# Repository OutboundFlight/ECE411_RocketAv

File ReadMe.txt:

Overview:

This GitHub provides documentation for the design, implemation, and use of the TinyAV
Amateur Avionics System. The TinyAV is a printed circuit board that includes a 
microcontroller, acellerometer, gyroscope, magnetometer, temperature sensor, flash
memory storage, and a rechargeable lithium-ion battery. It allows for a portable way 
to record flight data that can be use for flight analysis on model rockets.

----------------------------------------------------------------------------------------------

Table Of Contents:

Assignments - Team exercises assigned in ECE 411
Doc         - Project Proposals, Project Requirements, UML Diagrams, Testing Documentation, 
	      Project Schedules, & Bill Of Materials
Eagle       - Schematic & Board Layout Documentation
Launch_Data - Test Launch Raw Data & Analysis Graphs
Ref	    - Reference Documentation For Board Creation
Src	    - Libraries & Source Code For The TinyAv Board

----------------------------------------------------------------------------------------------

Useful Links:

Lab for Interconnected Devices: http://psu-epl.github.io/
Arduino Software: https://www.arduino.cc/

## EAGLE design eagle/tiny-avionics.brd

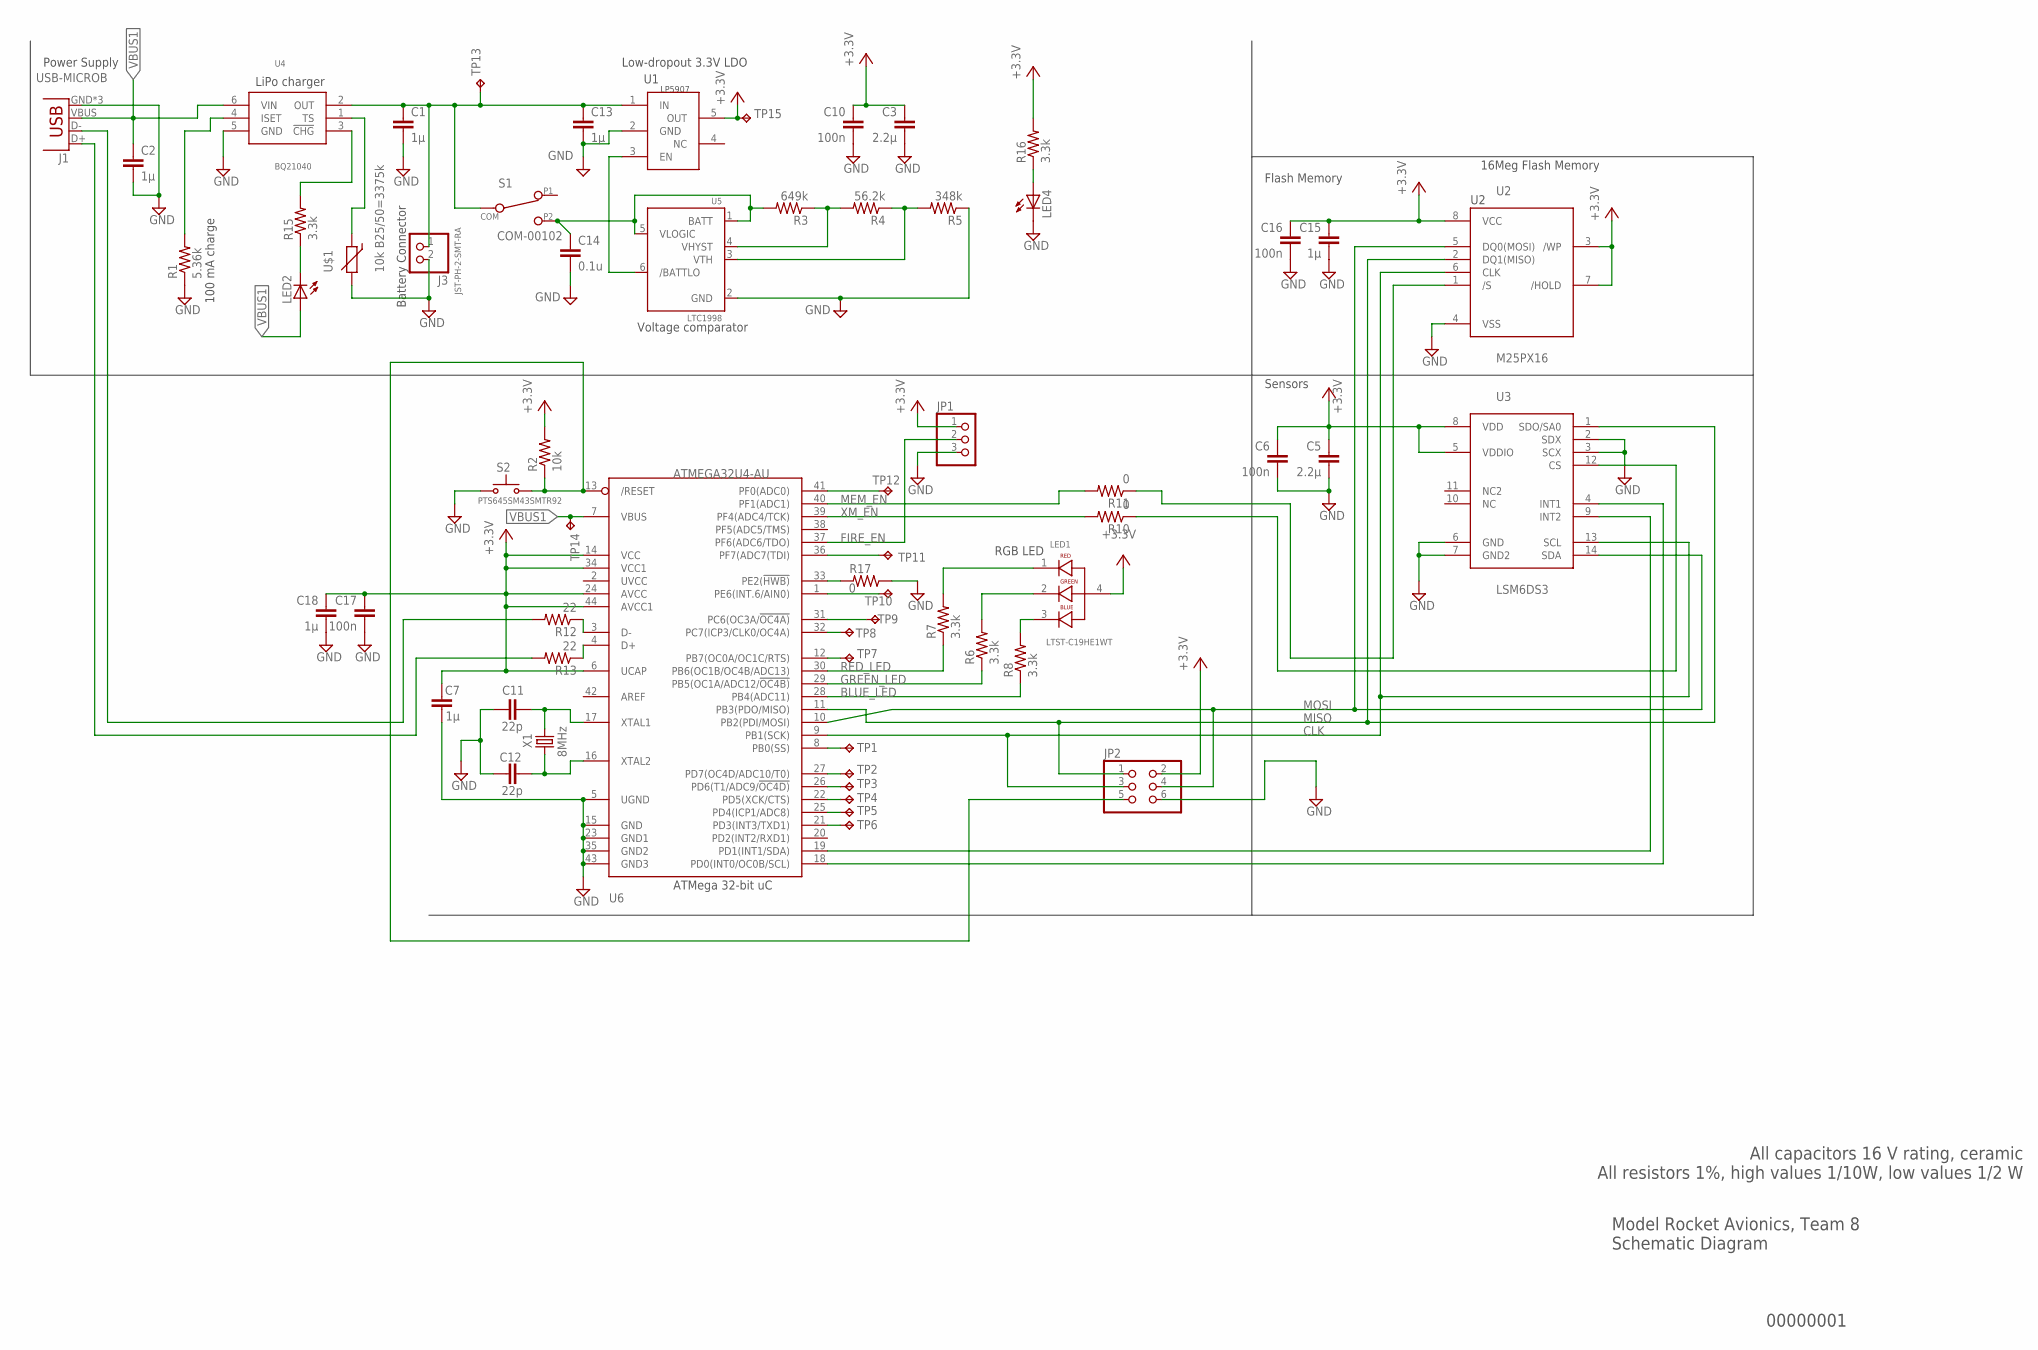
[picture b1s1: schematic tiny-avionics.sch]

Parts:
C1, C2, C7, C13, C15, C18: 1µ; C0603
C3, C5: 2.2µ; C0603
C6, C10, C16, C17: 100n; C0603
C11, C12: 22p; C0603
C14: 0.1u; C0603
J1: USB-MICROB
J3: JST-PH-2-SMT-RA
JP1: PINHD-1X3; 1X03
JP2: PINHD-2X3; 2X03
LED1: LTST-C19HE1WT; LEDSC85P160X160X35-4N
LED2, LED4: LEDCHIP-LED0603; CHIP-LED0603
R1: 5.36k; R0603
R2: 10k; R0603
R3: 649k; R0603
R4: 56.2k; R0603
R5: 348k; R0603
R6, R7, R8, R15, R16: 3.3k; R0603
R10, R11, R17: 0; R0603
R12, R13: 22; R0603
S1: COM-00102; ESWITCH
S2: PTS645SM43SMTR92; PTS645-SMD; MPN PTS645SM43SMTR92 LFS
TP1, TP2, TP3, TP4, TP5, TP6, TP7, TP8, TP9, TP10, TP11, TP12, TP13, TP14, TP15: TPTP08R; TP08R
U1: LP5907; SOT23-5L
U2: M25PX16; SO8
U3: LSM6DS3; LGA-14L
U4: BQ21040; SOT23-6L
U5: LTC1998; TSOT23-6
U6: ATMEGA32U4-AU; TQFP44
U$1: 10k B25/50=3375k; R0603
X1: 8MHz; ATS-SM; MPN ATS080B

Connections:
BLUE_LED: R8.1, U6.28 (PB4(ADC11))
CLK: JP2.3, U2.6 (CLK), U3.13 (SCL), U6.9 (PB1(SCK))
D+: J1.D+, R13.2
D-: J1.D-, R12.2
FIRE_EN: JP1.2, U6.37 (PF6(ADC6/TDO))
GND: C1.2, C2.2, C3.2, C5.2, C6.2, C7.2, C10.2, C11.2, C12.2, C13.2, C14.2, C15.2, C16.2, C17.2, C18.2, J1.GND, J1.MT1 (GND), J1.MT2 (GND), J3.2 (1), JP1.3, JP2.6, LED4.C, R1.1, R5.1, R17.1, S2.1, S2.2, U1.2 (GND), U2.4 (VSS), U3.2 (SDX), U3.3 (SCX), U3.6 (GND), U3.7 (GND2), U4.5 (GND), U5.2 (GND), U6.5 (UGND), U6.15 (GND), U6.23 (GND1), U6.35 (GND2), U6.43 (GND3), U$1.2
GREEN_LED: R6.1, U6.29 (PB5(OC1A/ADC12/!OC4B))
MEM_EN: R11.1, U2.1 (/S)
MISO: JP2.1, U2.2 (DQ1(MISO)), U3.1 (SDO/SA0), U6.11 (PB3(PDO/MISO))
MOSI: JP2.4, U2.5 (DQ0(MOSI)), U3.14 (SDA), U6.10 (PB2(PDI/MOSI))
unnamed: LED1.1, R7.2
unnamed: C11.1, U6.17 (XTAL1), X1.1
unnamed: JP2.5, R2.1, S2.3 (S), S2.4 (S), U6.13 (/RESET)
unnamed: R15.2, U4.3 (!CHG)
unnamed: C12.1, U6.16 (XTAL2), X1.2
unnamed: R12.1, U6.3 (D-)
unnamed: LED1.2, R6.2
unnamed: LED1.3, R8.2
unnamed: U4.1 (TS), U$1.1
unnamed: U3.4 (INT1), U6.18 (PD0(INT0/OC0B/SCL))
unnamed: U3.9 (INT2), U6.19 (PD1(INT1/SDA))
unnamed: R3.1, R4.2, U5.4 (VHYST)
unnamed: C1.1, C13.1, J3.1 (2), S1.2 (COM), TP13.TP, U1.1 (IN), U4.2 (OUT)
unnamed: R4.1, R5.2, U5.3 (VTH)
unnamed: C14.1, R3.2, S1.3 (P2), U5.1 (BATT), U5.5 (VLOGIC)
unnamed: U1.3 (EN), U5.6 (/BATTLO)
unnamed: R10.2, U6.39 (PF4(ADC4/TCK))
unnamed: R11.2, U6.40 (PF1(ADC1))
unnamed: R13.1, U6.4 (D+)
unnamed: LED2.C, R15.1
unnamed: R1.2, U4.4 (ISET)
unnamed: LED4.A, R16.1
unnamed: R17.2, U6.33 (PE2(!HWB))
RED_LED: R7.1, U6.30 (PB6(OC1B/OC4B/ADC13))
TP1: TP1.TP, U6.8 (PB0(SS))
TP2: TP2.TP, U6.27 (PD7(OC4D/ADC10/T0))
TP3: TP3.TP, U6.26 (PD6(T1/ADC9/!OC4D))
TP4: TP4.TP, U6.22 (PD5(XCK/CTS))
TP5: TP5.TP, U6.25 (PD4(ICP1/ADC8))
TP6: TP6.TP, U6.21 (PD3(INT3/TXD1))
TP7: TP7.TP, U6.12 (PB7(OC0A/OC1C/RTS))
TP8: TP8.TP, U6.32 (PC7(ICP3/CLK0/OC4A))
TP9: TP9.TP, U6.31 (PC6(OC3A/!OC4A))
TP10: TP10.TP, U6.1 (PE6(INT.6/AIN0))
TP11: TP11.TP, U6.36 (PF7(ADC7(TDI))
TP12: TP12.TP, U6.41 (PF0(ADC0))
VBUS1: C2.1, J1.VBUS, LED2.A, TP14.TP, U4.6 (VIN), U6.7 (VBUS)
VCC: C3.1, C5.1, C6.1, C7.1, C10.1, C15.1, C16.1, C17.1, C18.1, JP1.1, JP2.2, LED1.4, R2.2, R16.2, TP15.TP, U1.5 (OUT), U2.3 (/WP), U2.7 (/HOLD), U2.8 (VCC), U3.5 (VDDIO), U3.8 (VDD), U6.6 (UCAP), U6.14 (VCC), U6.24 (AVCC), U6.34 (VCC1), U6.44 (AVCC1)
XM_EN: R10.1, U3.12 (CS)

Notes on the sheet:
00000001
Model Rocket Avionics, Team 8 Schematic Diagram
Power Supply
Sensors
Flash Memory
All capacitors 16 V rating, ceramic All resistors 1%, high values 1/10W, low values 1/2 W
Battery Connector
Low-dropout 3.3V LDO
Voltage comparator
LiPo charger
ATMega 32-bit uC
16Meg Flash Memory
RGB LED
100 mA charge

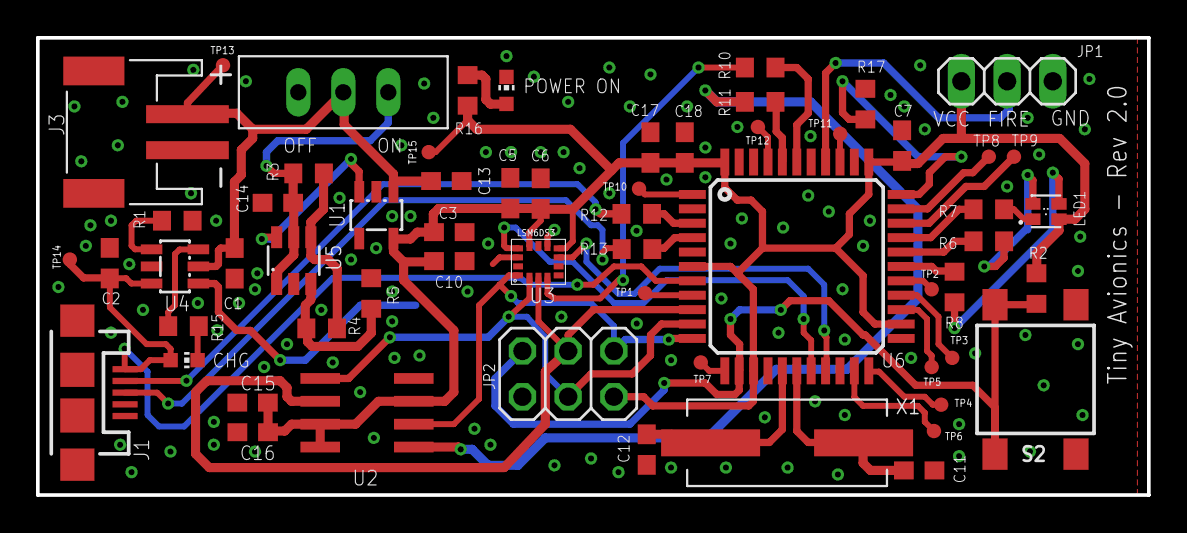
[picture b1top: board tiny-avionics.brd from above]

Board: 2 copper layers, 61.7 x 25.4 mm, 62 parts (1 on the bottom side), 49 nets.

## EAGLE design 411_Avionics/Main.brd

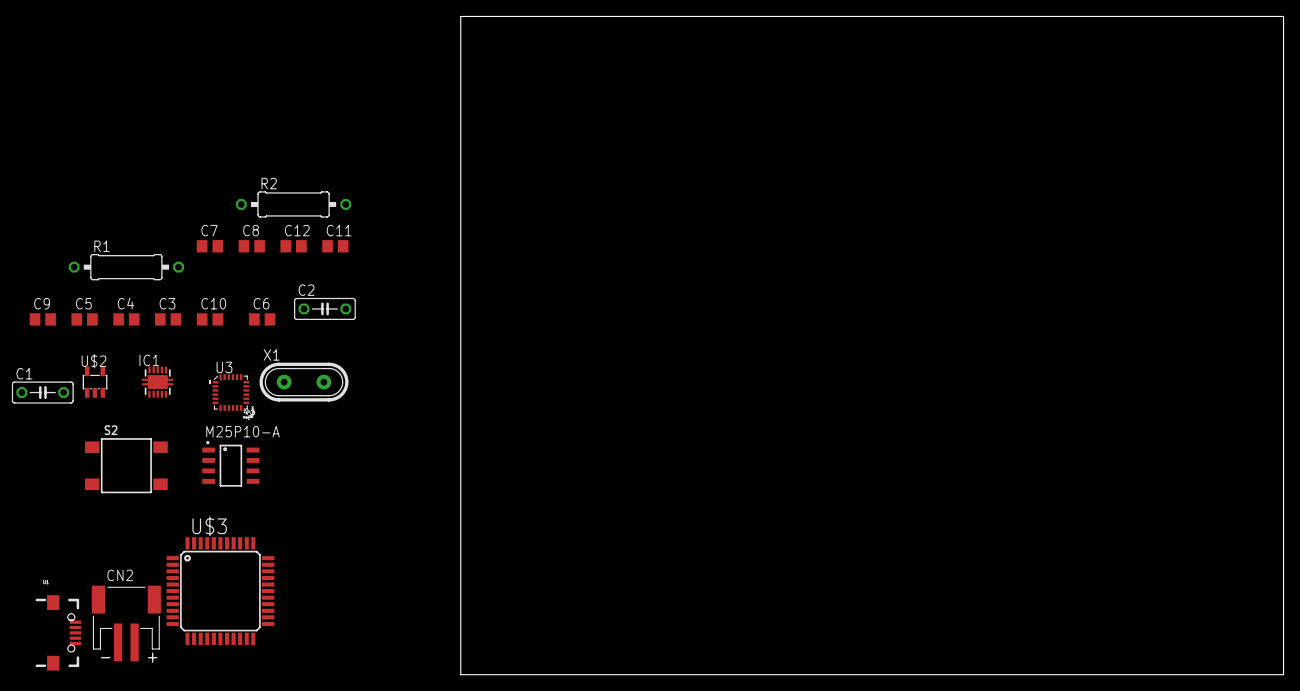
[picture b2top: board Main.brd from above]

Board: 2 copper layers, 100.0 x 80.0 mm, 23 parts (0 on the bottom side), 20 nets, no tracks yet.

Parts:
C1, C2: 1µ; C050-025X075
C3: 4.7µ; C0805
C4: .22µ; C0805
C5, C9: 2.2µ; C0805
C6, C10: 100n; C0805
C7: 1µ; C0805
C8: 10u; C0805
C11, C12: 22p; C0805
CN2: JST-PH-2-SMT-RA
IC1: BQ24022; DRC-S-PVSON-N10
R1: 4k'; 0309/12
R2: 10k; 0309/12
S2: PTS645SM43SMTR92; PTS645-SMD
U1: USB_In; USB-MICRO-SMD
U3: LSM9DS0; LGA-24
U$1: M25P10-AVMN6TP_TR; SOIC127P600X175-8N
U$2: LP5907; SOT23-5L
U$3: ATMEGA32U4-AU; TQFP44
X1: 8MHz; HC49

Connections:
CLK: U3.21, U$1.6, U$3.9
D+: U1.D+1, U$3.4
D-: U1.D-1, U$3.3
GND: C1.2, C2.2, C3.1, C5.2, C6.2, C7.2, C8.2, C9.2, C10.2, C11.2, C12.2, CN2.2, IC1.5, IC1.7, IC1.8, IC1.9, R1.1, U1.GND1, U3.2, U3.3, U3.4, U3.5, U3.6, U$1.4, U$2.2, U$3.5, U$3.15, U$3.23, U$3.33, U$3.35, U$3.43
GYR_EN: U3.19, U$3.38
MEM_EN: U$1.1, U$3.40
MISO: U3.22, U3.23, U$1.2, U$3.11
MOSI: U3.24, U$1.5, U$3.10
unnamed: C2.1, IC1.2, U1.VBUS1
unnamed: C11.1, U$3.17, X1.1
unnamed: R2.2, S2.3, S2.4, U$3.13
unnamed: IC1.6, R1.2
unnamed: C12.1, U$3.16, X1.2
unnamed: C8.1, S2.1, S2.2
unnamed: C3.2, U3.7
unnamed: C4.2, U3.8
unnamed: C4.1, U3.9
unnamed: C1.1, CN2.1, IC1.10, U$2.1, U$2.3
VCC: C5.1, C6.1, C7.1, C9.1, C10.1, R2.1, U3.15, U3.16, U3.17, U3.18, U$1.3, U$1.7, U$1.8, U$2.5, U$3.6, U$3.14, U$3.24, U$3.34, U$3.44
XM_EN: U3.20, U$3.39

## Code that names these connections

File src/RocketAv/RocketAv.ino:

#include <SPI.h>
#include <Adafruit_LSM9DS0.h>
#include <Adafruit_Sensor.h>
#include <tinyav_spiflash.h>

#define SENSOR_STALL 2

//#define SERIAL_DEBUG

// Define enable pins
#define MEM_EN 22
#define GYR_EN A2
#define XM_EN A3

#define BAUD 115200

// Hardware SPI setup for sensor
Adafruit_LSM9DS0 lsm = Adafruit_LSM9DS0(XM_EN, GYR_EN);

typedef struct sensor_sample {
  long timestamp;
  int xm_x;
  int xm_y;
  int xm_z;
  int gyr_x;
  int gyr_y;
  int gyr_z;
  int mag_x;
  int mag_y;
  int mag_z;
  int temp;
  char line;
}sensor_sample;

int samples_per_page = PAGE_SIZE/sizeof(sensor_sample);

union page
{
  sensor_sample entries[12];
  uint8_t bytes [PAGE_SIZE];
} pdata;

void setupSensor()
{
  // 1.) Set the accelerometer range
  //lsm.setupAccel(lsm.LSM9DS0_ACCELRANGE_2G);
  //lsm.setupAccel(lsm.LSM9DS0_ACCELRANGE_4G);
  //lsm.setupAccel(lsm.LSM9DS0_ACCELRANGE_6G);
  //lsm.setupAccel(lsm.LSM9DS0_ACCELRANGE_8G);
  lsm.setupAccel(lsm.LSM9DS0_ACCELRANGE_16G);
  
  // 2.) Set the magnetometer sensitivity
  lsm.setupMag(lsm.LSM9DS0_MAGGAIN_2GAUSS);
  //lsm.setupMag(lsm.LSM9DS0_MAGGAIN_4GAUSS);
  //lsm.setupMag(lsm.LSM9DS0_MAGGAIN_8GAUSS);
  //lsm.setupMag(lsm.LSM9DS0_MAGGAIN_12GAUSS);

  // 3.) Setup the gyroscope
  //lsm.setupGyro(lsm.LSM9DS0_GYROSCALE_245DPS);
  //lsm.setupGyro(lsm.LSM9DS0_GYROSCALE_500DPS);
  lsm.setupGyro(lsm.LSM9DS0_GYROSCALE_2000DPS);
}
 spiflash flash;

int sample_number;
  char mode;
int current_page;

void setup() 
{
  Serial.begin(BAUD);
  Serial.println("~~RocketAV software version 1.0~~");
  flash.init(MEM_EN);


  Serial.print("Please select: [i]dle mode, [l]aunch mode, [d]ownload data, [e]rase memory? ");
  if (!lsm.begin()) {
    Serial.println("Oops ... unable to initialize the LSM9DS0. Check your wiring!");
  }


  setupSensor();
  sample_number = 0;
  mode = 'i';
  flash.unprotect();
}

void loop() 
{
// Wait for USB port communication

  char input;
  int nextpage;
  if(Serial1)
  {
  if(Serial.available())
  { 
    input=Serial.read();
    switch (input)
    {
      case 'i':
        mode = 'i';
        Serial.println("Entering idle mode...");
        break;
      
      case 'l':
        mode = 'l';
        sample_number = 0;
        Serial.println("Entering launch mode...");
        Serial.println("Beginning 60s launch timer...");
        delay(120000);
        break;
        
      case 'd':
        nextpage = 0;
        for(int i = 0; i < PAGE_SIZE; i++) {pdata.bytes[i] = 0;}
        Serial.print("Reading from flash head at 0x");
        Serial.println(flash.getHead(), HEX);
        for(uint16_t i = 0; i < flash.getHead(); i++)
        {

//          Serial.print("Reading page ");
//          Serial.println(i);
          uint32_t addr = flash.readPage(i, pdata.bytes);
//          Serial.print("Actual address ");
//          Serial.println(addr, HEX);
          for (int j = 0; j < samples_per_page; j++)
          {
            serialPrintSample(pdata.entries[j]);
          }          
        };

        break;
      case 'e':
        Serial.print("Erasing memory... ");
        flash.chipErase();
        Serial.println("Done!");
        break;
      }
      Serial.print("Please select: [i]dle mode, [l]aunch mode, [d]ownload data, [e]rase memory? ");
    }
  }
    
  if (mode == 'i')
  {
    ;
  }  
  else if (mode == 'l')
  {
    delay(SENSOR_STALL);
    lsm.read();
    sensor_sample curr;

    curr.timestamp = millis();
    curr.xm_x = lsm.accelData.x;
    curr.xm_y = lsm.accelData.y;
    curr.xm_z = lsm.accelData.z;
    curr.gyr_x = lsm.gyroData.x;
    curr.gyr_y = lsm.gyroData.y;
    curr.gyr_z = lsm.gyroData.z;
    curr.mag_x = lsm.magData.x;
    curr.mag_y = lsm.magData.y;
    curr.mag_z = lsm.magData.z;
    curr.temp = lsm.temperature;
    curr.line = 0xA;
    pdata.entries[sample_number] = curr;

    #ifdef SERIAL_DEBUG
    if(Serial1)
    {
      Serial.print("Sample ");
      Serial.print(sample_number);
      Serial.print(":");
      serialPrintSample(curr);
    }
    #endif

    sample_number++;

    if(sample_number >= samples_per_page)
    {
      int err;
      err = flash.writeSequentialPage(pdata.bytes, PAGE_SIZE);
      
      sample_number = 0;
      for(int i = 0; i < PAGE_SIZE; i++) {pdata.bytes[i] = 0;}

    #ifdef SERIAL_DEBUG
    Serial.print("Printing page");
    Serial.println(err);
    Serial.print("Head location: ");
    Serial.println(flash.getHead(), HEX);
    Serial.print("Address equivalent: ");
    Serial.println(((uint32_t)flash.getHead()) << 8, HEX);
    #endif
    }

  }
}


void serialPrintSample(sensor_sample curr_data)
{
  Serial.print(curr_data.timestamp);
  Serial.print(',');
  Serial.print(curr_data.xm_x);
  Serial.print(',');
  Serial.print(curr_data.xm_y);
  Serial.print(',');   
  Serial.print(curr_data.xm_z);
  Serial.print(','); 
  Serial.print(curr_data.gyr_x);
  Serial.print(',');
  Serial.print(curr_data.gyr_y);
  Serial.print(',');
  Serial.print(curr_data.gyr_z);
  Serial.print(',');
  Serial.print(curr_data.mag_x);
  Serial.print(',');
  Serial.print(curr_data.mag_y);
  Serial.print(',');
  Serial.print(curr_data.mag_z);
  Serial.print(',');
  Serial.println(curr_data.temp);
}

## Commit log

2016-10-22 hey, look here!
2016-10-22 Created Eagle project for schematic/layout
2016-10-25 Added project requirements document Rev 1.0
2016-10-29 Updated master schematic to have power management front end.
2016-10-29 .... Actually added the .sch file this time.
2016-10-30 Worked on schematic, connected memory
2016-10-30 Updated sensor connections on schematic.
2016-10-30 Lifted flash memory unused pins in schematic
2016-10-30 Almost finished schematic, left to be done:
    -Connect MUX to proper pins
    -Processor Interfacing
    -Still need to change USB connection
    -Finish footprints
2016-10-31 Schematic reorganized and touched up
2016-10-31 Minor changes to schematic power logic. Also added a couple bypass capacitors to output of LM317.
2016-11-01 Added pin headers to read memory contents. Change before release!
2016-11-02 ECE411: Began reworking schematic, removed cell protection and added LDO to library and schematic.
2016-11-03 Replaced ATTiny with ATMega32U4. Hooked up LDO.
2016-11-03 Added RESET switch and Oscillator to schematic
2016-11-03 Re-made Main.brd file to reflect most recent schematic.
2016-11-03 Final Proposal Documents
2016-11-03 Commented changes to be made from design review, removed temp files
2016-11-04 Added more design review notes
2016-11-04 Started library of custom footprints. LTC1998 comparator for undervoltage protection. User power switch.
2016-11-04 Changed to micro-USB B connector from SparkFun library
2016-11-05 Worked on notes given at previous design review. Did not finish them all, still some left to be done.
2016-11-05 Added RGB LED & resolved several ERC errors
2016-11-05 Project Schedule: Task allocation still needs work
2016-11-07 Connected interrupts and started layout
2016-11-07 Created ground plane, started draft layout, deleted temp files
2016-11-07 Updated schedule
2016-11-08 Reworked layout a bit. Still need to connect memory and sensors.
2016-11-08 Finished board layout!! Still have to create ground planes and add ground vias, but other than that it's all done. Hooray!
2016-11-08 Changed starting milestone to indicate team number
2016-11-08 More layout work. All nodes connected, still need to run through DRC and deal with all that bs.
2016-11-08 Made some changes to silkscreen layer, fixed package text size.
2016-11-08 Finished preliminary board layout! Passed OSHParks DRC, hooray!
2016-11-09 Layout Review #1 With Andrew:
    -changed all 0805 packages to 0603 (made a lot more room)
    -made vias significantly smaller (made a lot more room)
    -updated layout to reflect these changes, no DRC issues
    We should consider hooking up the status pins of our battery charger to
    LEDs. Should also consider increasing the value of our current limiting
    resistors from the processor.
2016-11-09 Deleted temp files that were clogging up our repo!
2016-11-10 Updated a few oopsies on board layout. A couple nodes not connected, switch on bottom layer. Added a couple more vias as well.
2016-11-11 Added 3-pin pad for firing circuit
2016-11-11 Kind of ugly, but I got the ignition switch hooked up.
    Should work alright! Board is ready to be shipped off!
2016-11-11 Updated current limiting resistors to 0805 package. Also fixed some oopsies on the layout (extra traces).
2016-11-16 Added resistors to D+/D-, removed incorrect reset button cap, fixed RGB LED VCC
2016-11-17 Lots of changes to layout!
    -Added 6 pin header
    -Added status LEDs
    -Added Power LEDs`
2016-11-17 Added 0 ohm resistor to #HWB line. Added test points to unpopulated GPIO.
2016-11-17 Added test points to accelerometer DRDY and DENB
2016-11-17 Fixed silkscreen
2016-11-17 Some silk screen touches to BRD file.
    Ready to ship off.
2016-11-17 Removed confusing redundant board file
2016-11-17 Added Homework 5 - System Design and Modeling
2016-11-17 Added Homework 5: System Design and Modeling
2016-11-24 Added PDF version of Schematic for reference purposes
2016-11-24 Made changes to schematic to display IC names
2016-11-24 Reorganized folders
2016-11-24 Added Test Plan
2016-11-24 Fixed title page of test plan
2016-11-28 Tried covering the ground vias with soldermask since they're exposed currently and it's making me go crazy I stay up late at night thinking about it.
2016-12-01 Reorganized Folders & Documentation. Changed documentation to be consistent with project name
2016-12-01 Added pdf for board layout
2016-12-01 Re-added board file
2016-12-04 Rerouted /PG pin on BQ24022. Corrected symbol and added to eagle library.
2016-12-04 Rearranged repo
2016-12-06 Updated requirements document
2016-12-07 Uploaded custom SPI library source files
2016-12-07 Comments and improvements to spiflash lib
2016-12-07 Added Readme & board PDF
2016-12-07 Added general functional code outline
2016-12-07 Added makefile to create zip for arduino libs
2016-12-07 Added InitialSetup ReadMe file
2016-12-07 Updated ReadMe file
2016-12-07 Uploaded sensor libraries
2016-12-07 Makefile for generating Arduino zips. RocketAv script updated.
2016-12-07 Added zip file for spiflash library.
2016-12-07 Pushing for Aaron -
    Bug hunting main program sketch.
2016-12-07 fixed bug with address-generating macros
2016-12-07 Added Bill Of Materials
2016-12-07 Working main sketch. Fixed overflow, simplified spiflash library.
2016-12-08 Added launch data
2016-12-08 Saved calibration data for xm, mag
2016-12-08 Added launch files
2016-12-08 Added gyro calibration tests
2016-12-08 Fixed bug with sensor calibration
2016-12-08 Formatted launch file correctly
2016-12-08 Fixed sensor cal bug
2016-12-08 New gyro test for blue board
2016-12-08 Added new green board gyro test
2016-12-08 Added overall xm tests for blue and green
2016-12-08 Added specifix xm tests for all directions
2016-12-08 Reorganized cal data and corrected format. Added calibration scripts.
2016-12-08 Added launch data for Thursday, 12/08/2016
2016-12-08 UML diagrams added
2016-12-08 Added plots for data visualization. Matlab acceleration and rotation scripts.
2016-12-08 Project schedule and UML updated
2016-12-08 Reorganized repo, added new ReadMe
2016-12-08 Updated readme with launch procedure
2016-12-08 Updated 'ref' ReadMe & moved BOM to correct location
2016-12-08 Fixed merge issues. Andy's a dingus.
2016-12-16 Added device for charging chip, and created footprint and device for sensor.
    Also began reworking schematic.
2016-12-18 Deleted assignments folder
2016-12-18 Reorganized files for transition to independent project
2016-12-18 Reverted board files on master to known-good version
2016-12-18 Schematic work and created new device for 8-pin SPI memory chip.
2016-12-18 Working changes to schematic and layout.
2016-12-21 Continued layout work.
2016-12-21 More layout work. Removed a bypass capacitor we didn't really need.
2016-12-22 Finished new board layout with no DRC errors.
    It's a little smaller, but not much smaller. Made an effort to spread out
    components for easier assembly, however. Layout is also much more
    intuitive.
2016-12-23 Some minor changes.
2016-12-28 Added SMD crystal device and replaced on board
2016-12-28 Added thermistor to bottom of board
2017-01-01 Went through a few of the issues Andrew raised. Still some that need to be addressed.
2017-01-11 Finished layout rework from 2nd design review.
    Still left to do:
    -Change 0603 footprints to RCL custom library 0603s
    -Additional schematic work
2017-02-04 Fixed remaining design rev issues. Slightly thinner pads for LSM6DS0 to comply with OshPark DRC.
2017-02-15 Updated libraries, readme and file structure for Rev 2.0
2017-02-15 Added documentation from google drive. Added board and schematic images.

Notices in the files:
parts and their libraries:
switch-ck: Copyright (C) 2011, Bob Starr
SparkFun-Connectors: Licensing: Creative Commons ShareAlike 4.0 International - https://creativecommons.org/licenses/by-sa/4.0
